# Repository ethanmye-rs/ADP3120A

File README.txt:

This is a ADP3120A based H Bridge Driver. It utilizes 2 ADP3120A Gate drivers to drive 4 N Channel MOSFETs, rated for up to 30V and 6A each. The board is less than one square inch and the BOM + PCB can be purchased for around $10 in singles quanitity from Digikey and OSHpark.

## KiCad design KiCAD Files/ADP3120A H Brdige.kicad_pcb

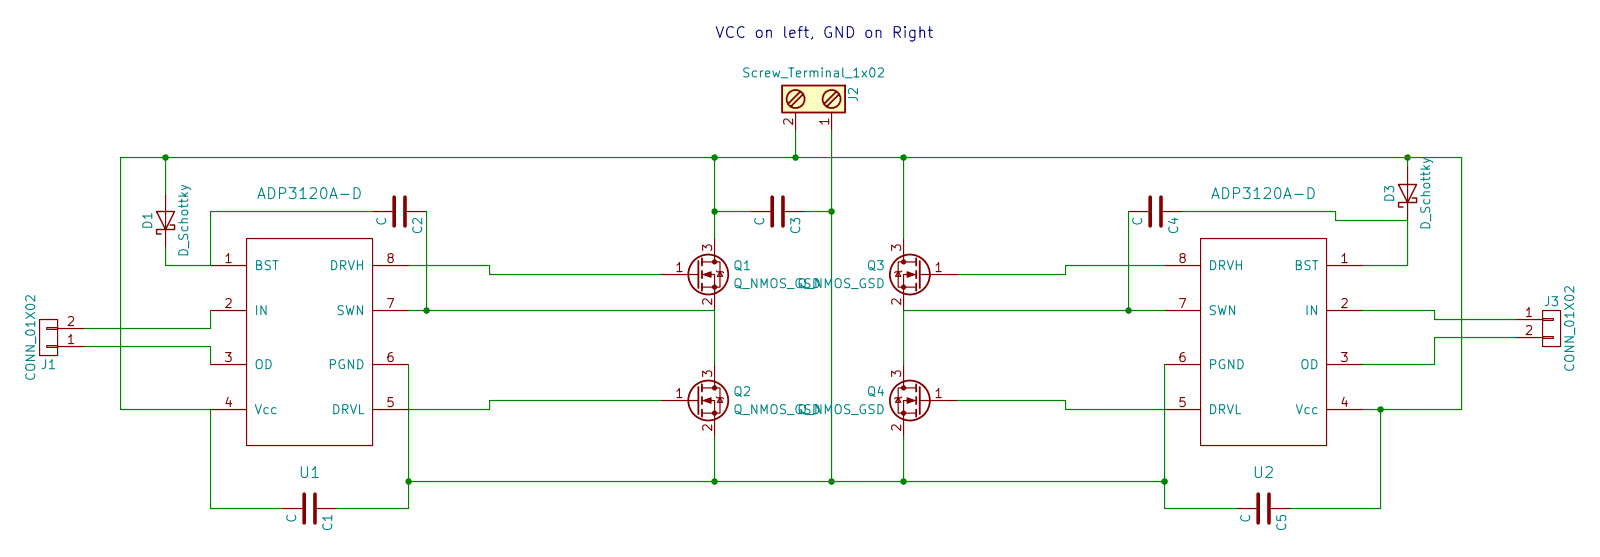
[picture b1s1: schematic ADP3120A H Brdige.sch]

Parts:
C1, C2, C3, C4, C5: C; C_1206_HandSoldering
D1, D3: D_Schottky; D_SMA_Handsoldering
J1, J3: CONN_01X02; Pin_Header_Straight_1x02_Pitch2.54mm
J2: Screw_Terminal_1x02; Pin_Header_Straight_1x02_Pitch2.54mm
Q1, Q2, Q3, Q4: Q_NMOS_GSD; SOT-23
U1, U2: ADP3120A-D; SOIC-8_3.9x4.9mm_Pitch1.27mm

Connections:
unnamed: C1.1, C3.1, C5.2, J2.1, Q2.2 (S), Q4.2 (S), U1.6 (PGND), U2.6 (PGND)
unnamed: C1.2, C3.2, C5.1, D1.2 (A), D3.2 (A), J2.2, Q1.3 (D), Q3.3 (D), U1.4 (Vcc), U2.4 (Vcc)
unnamed: C2.1, Q1.2 (S), Q2.3 (D), U1.7 (SWN)
unnamed: C2.2, D1.1 (K), U1.1 (BST)
unnamed: C4.1, D3.1 (K), U2.1 (BST)
unnamed: C4.2, Q3.2 (S), Q4.3 (D), U2.7 (SWN)
unnamed: J1.1, U1.3 (OD)
unnamed: J1.2, U1.2 (IN)
unnamed: J3.1, U2.2 (IN)
unnamed: J3.2, U2.3 (OD)
unnamed: Q1.1 (G), U1.8 (DRVH)
unnamed: Q2.1 (G), U1.5 (DRVL)
unnamed: Q3.1 (G), U2.8 (DRVH)
unnamed: Q4.1 (G), U2.5 (DRVL)

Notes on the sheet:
VCC on left, GND on Right

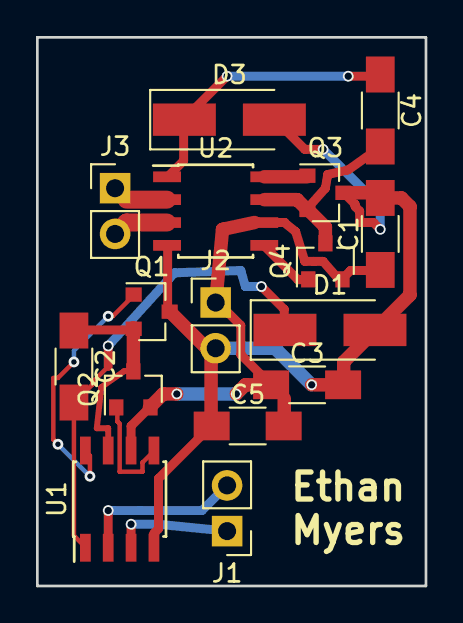
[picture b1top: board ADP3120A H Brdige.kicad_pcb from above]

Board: 2 copper layers, 21.6 x 30.5 mm, 16 parts (0 on the bottom side), 14 nets.

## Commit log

2017-07-12 folder reorganization
2017-07-12 readme
2017-07-12 Create LICENSE
2017-07-18 updated with code.
